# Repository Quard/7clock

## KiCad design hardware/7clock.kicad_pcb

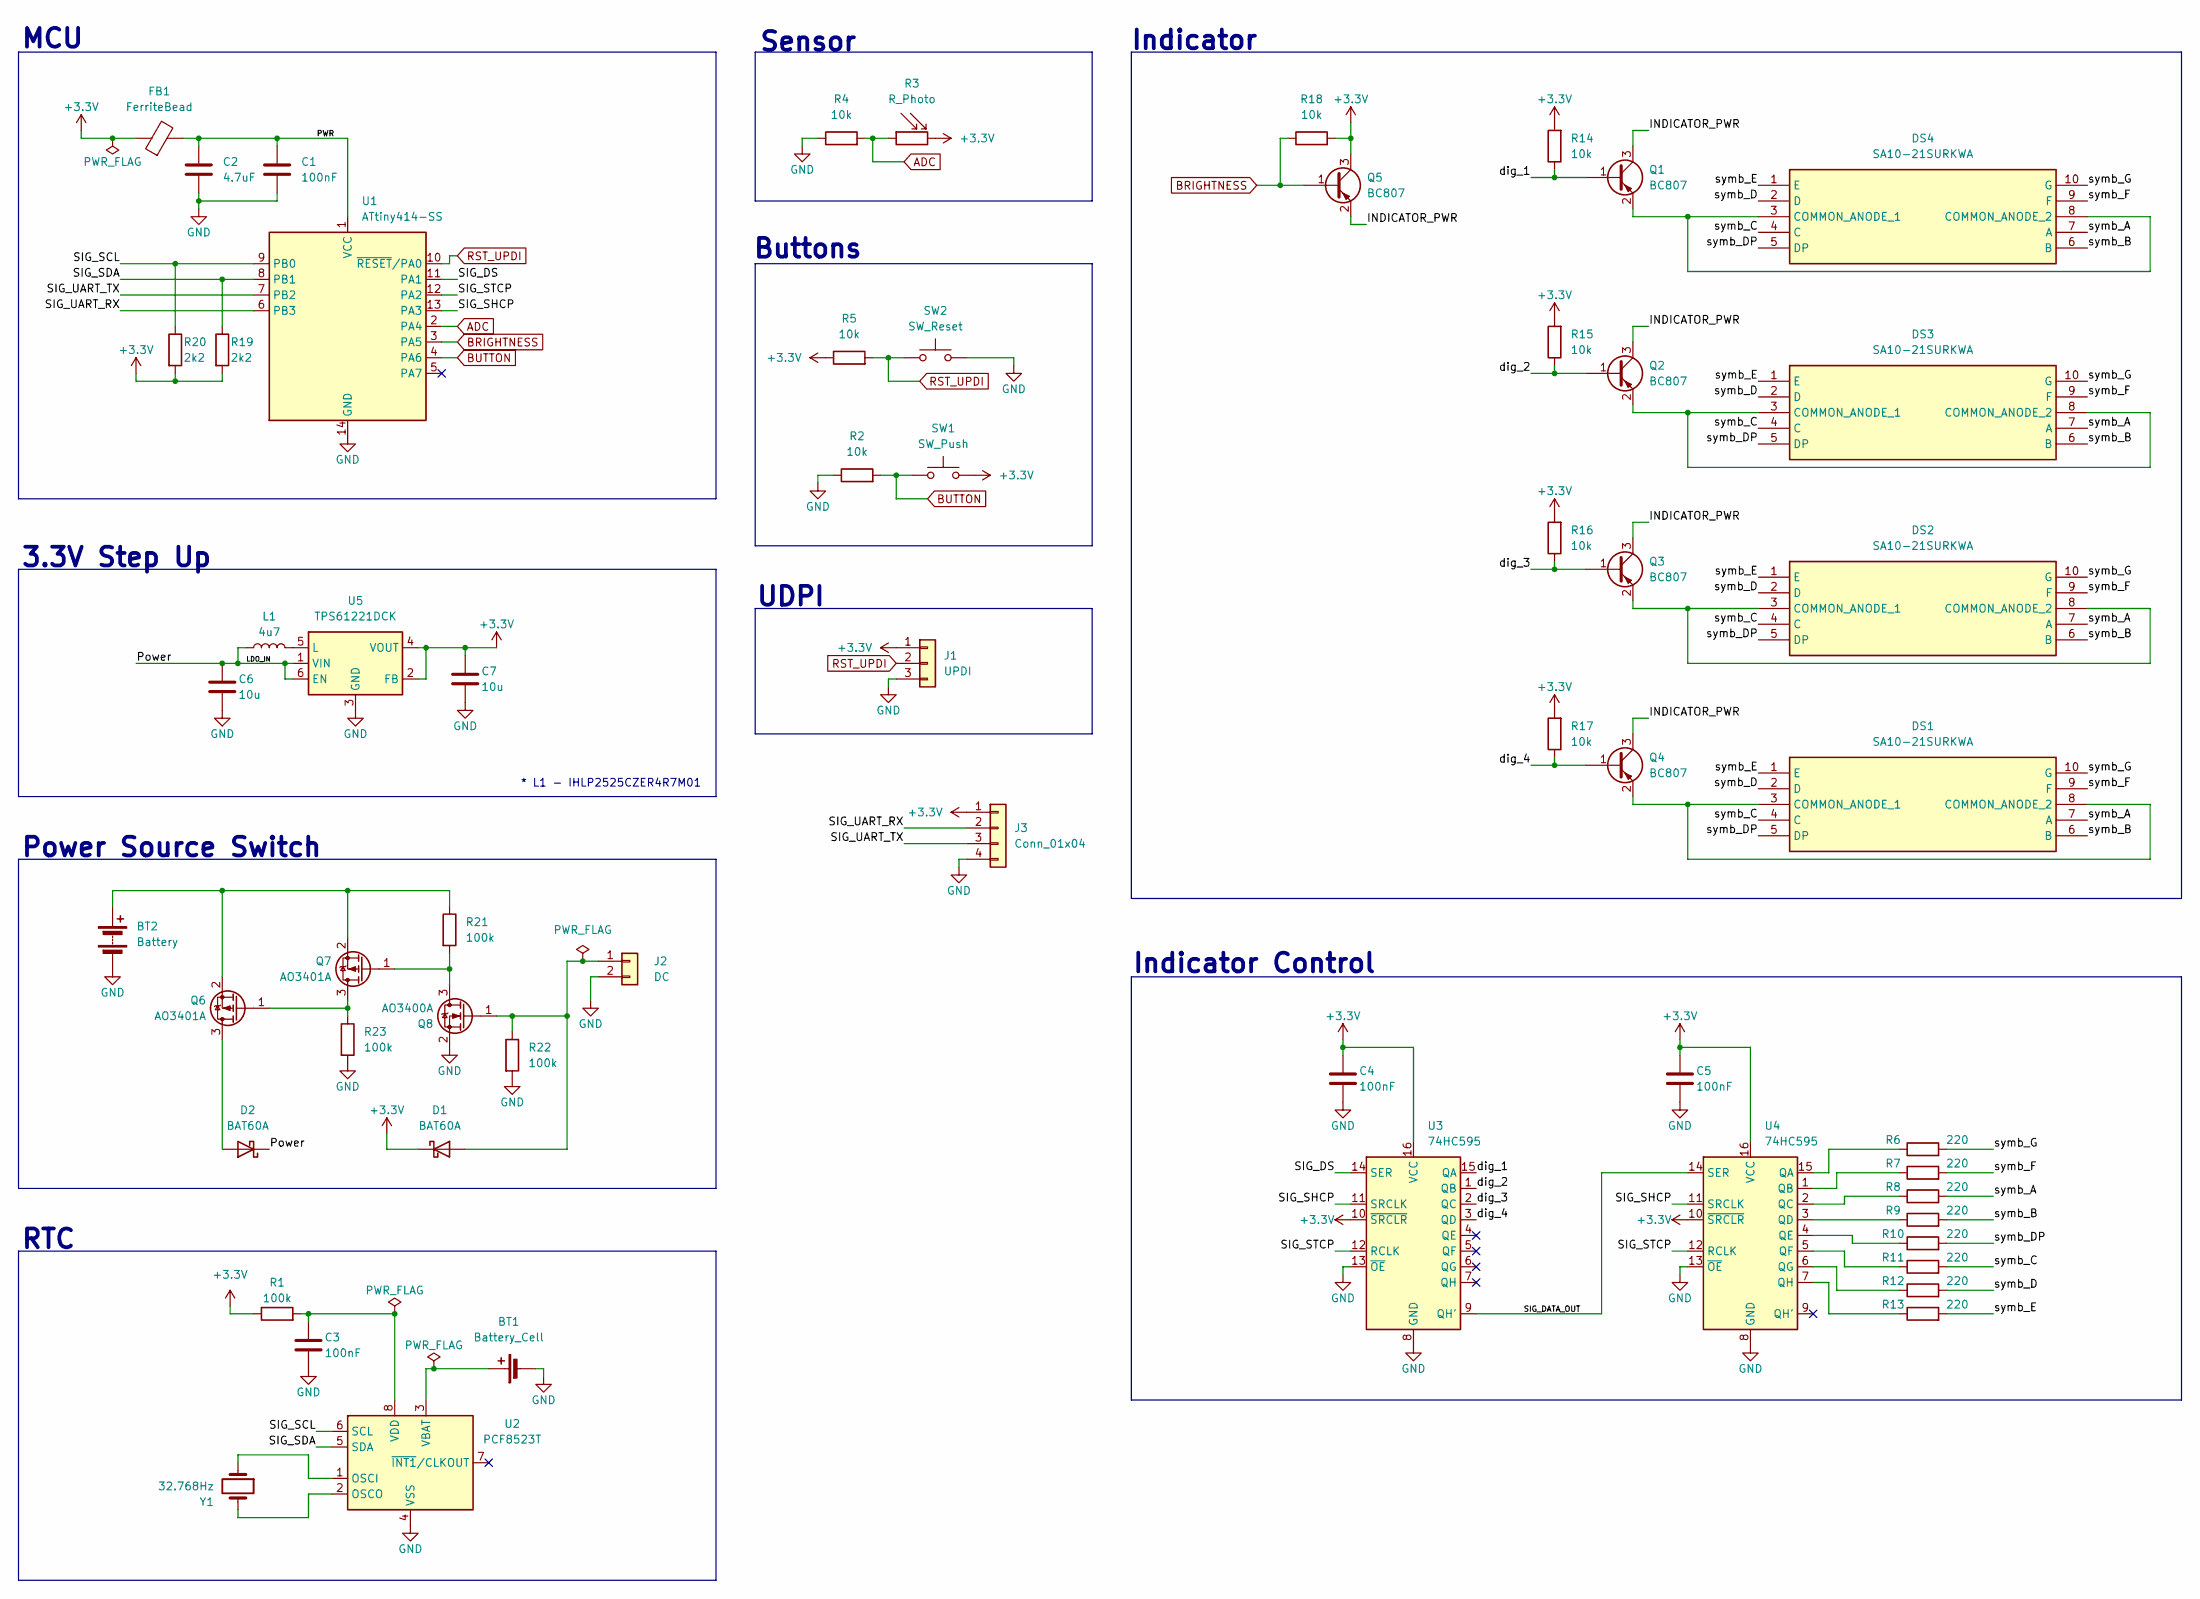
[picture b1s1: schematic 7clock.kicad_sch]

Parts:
BT1: Battery_Cell; CR1220D-011
BT2: Battery; PinHeader_1x02_P2.54mm_Vertical
C1, C3, C4, C5: 100nF; C_0603_1608Metric
C2: 4.7uF; C_0805_2012Metric
C6, C7: 10u; C_0805_2012Metric
D1, D2: BAT60A; D_SOD-323
DS1, DS2, DS3, DS4: SA10-21SURKWA; DIP3040W75P254L2400H1050Q10N; Manufacturer_Part_Number SA10-21SURKWA; Mouser Part Number 604-SA10-21SURKWA
FB1: FerriteBead; L_0603_1608Metric
J1: UPDI; PinHeader_1x03_P2.54mm_Vertical
J2: DC; PinHeader_1x02_P2.54mm_Vertical
J3: Conn_01x04; PinHeader_1x04_P2.54mm_Vertical
L1: 4u7; L_Vishay_IHLP-2525
Q1, Q2, Q3, Q4, Q5: BC807; SOT-23
Q6, Q7: AO3401A; SOT-23
Q8: AO3400A; SOT-23
R1, R21, R22, R23: 100k; R_0603_1608Metric
R2, R4, R5, R14, R15, R16, R17, R18: 10k; R_0603_1608Metric
R3: R_Photo; PinHeader_1x02_P2.54mm_Vertical
R6, R7, R8, R9, R10, R11, R12, R13: 220; R_0603_1608Metric
R19, R20: 2k2; R_0603_1608Metric
SW1: SW_Push; SW_SPST_SKQG_WithoutStem
SW2: SW_Reset; SW_SPST_CK_RS282G05A3
U1: ATtiny414-SS; SOIC-14_3.9x8.7mm_P1.27mm
U2: PCF8523T; SOIC-8_3.9x4.9mm_P1.27mm
U3, U4: 74HC595; SO-16_3.9x9.9mm_P1.27mm
U5: TPS61221DCK; Texas_R-PDSO-G6
Y1: 32.768Hz; Crystal_C38-LF_D3.0mm_L8.0mm_Horizontal

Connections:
+3.3V: C4.1, C5.1, C7.1, D1.1 (K), FB1.1, J1.1, J3.1, Q5.3 (C), R1.1, R3.2, R5.1, R14.2, R15.2, R16.2, R17.2, R18.2, R19.2, R20.2, SW1.2, U3.10 (~SRCLR), U3.16 (VCC), U4.10 (~SRCLR), U4.16 (VCC), U5.2 (FB), U5.4 (VOUT)
/INDICATOR_PWR: Q1.3 (C), Q2.3 (C), Q3.3 (C), Q4.3 (C), Q5.2 (E)
/LDO_IN: C6.1, D2.1 (K), L1.1, U5.1 (VIN), U5.6 (EN)
/PWR: C1.1, C2.1, FB1.2, U1.1 (VCC)
/SIG_DATA_OUT: U3.9 (QH'), U4.14 (SER)
/SIG_DS: U1.11 (PA1), U3.14 (SER)
/SIG_SCL: R20.1, U1.9 (PB0), U2.6 (SCL)
/SIG_SDA: R19.1, U1.8 (PB1), U2.5 (SDA)
/SIG_SHCP: U1.13 (PA3), U3.11 (SRCLK), U4.11 (SRCLK)
/SIG_STCP: U1.12 (PA2), U3.12 (RCLK), U4.12 (RCLK)
/SIG_UART_RX: J3.2, U1.6 (PB3)
/SIG_UART_TX: J3.3, U1.7 (PB2)
/dig_1: Q1.1 (B), R14.1, U3.15 (QA)
/dig_2: Q2.1 (B), R15.1, U3.1 (QB)
/dig_3: Q3.1 (B), R16.1, U3.2 (QC)
/dig_4: Q4.1 (B), R17.1, U3.3 (QD)
/symb_A: DS1.7 (A), DS2.7 (A), DS3.7 (A), DS4.7 (A), R8.2
/symb_B: DS1.6 (B), DS2.6 (B), DS3.6 (B), DS4.6 (B), R9.2
/symb_C: DS1.4 (C), DS2.4 (C), DS3.4 (C), DS4.4 (C), R11.2
/symb_D: DS1.2 (D), DS2.2 (D), DS3.2 (D), DS4.2 (D), R12.2
/symb_DP: DS1.5 (DP), DS2.5 (DP), DS3.5 (DP), DS4.5 (DP), R10.2
/symb_E: DS1.1 (E), DS2.1 (E), DS3.1 (E), DS4.1 (E), R13.2
/symb_F: DS1.9 (F), DS2.9 (F), DS3.9 (F), DS4.9 (F), R7.2
/symb_G: DS1.10 (G), DS2.10 (G), DS3.10 (G), DS4.10 (G), R6.2
ADC: R3.1, R4.2, U1.2 (PA4)
BRIGHTNESS: Q5.1 (B), R18.1, U1.3 (PA5)
BUTTON: R2.2, SW1.1, U1.4 (PA6)
GND: BT1.2 (-), BT2.2 (-), C1.2, C2.2, C3.2, C4.2, C5.2, C6.2, C7.2, J1.3, J2.2, J3.4, Q8.2 (S), R2.1, R4.1, R22.2, R23.2, SW2.2, U1.14 (GND), U2.4 (VSS), U3.8 (GND), U3.13 (~OE), U4.8 (GND), U4.13 (~OE), U5.3 (GND)
unnamed: BT1.1 (+), U2.3 (VBAT)
unnamed: BT2.1 (+), Q6.2 (S), Q7.2 (S), R21.1
unnamed: D1.2 (A), J2.1, Q8.1 (G), R22.1
unnamed: D2.2 (A), Q6.3 (D)
unnamed: DS1.3 (COMMON_ANODE_1), DS1.8 (COMMON_ANODE_2), Q4.2 (E)
unnamed: DS2.3 (COMMON_ANODE_1), DS2.8 (COMMON_ANODE_2), Q3.2 (E)
unnamed: DS3.3 (COMMON_ANODE_1), DS3.8 (COMMON_ANODE_2), Q2.2 (E)
unnamed: DS4.3 (COMMON_ANODE_1), DS4.8 (COMMON_ANODE_2), Q1.2 (E)
unnamed: Q6.1 (G), Q7.3 (D), R23.1
unnamed: Q7.1 (G), Q8.3 (D), R21.2
unnamed: U2.1 (OSCI), Y1.1
unnamed: U2.2 (OSCO), Y1.2
unnamed: C3.1, R1.2, U2.8 (VDD)
unnamed: R6.1, U4.15 (QA)
unnamed: R7.1, U4.1 (QB)
unnamed: R8.1, U4.2 (QC)
unnamed: R9.1, U4.3 (QD)
unnamed: R10.1, U4.4 (QE)
unnamed: R11.1, U4.5 (QF)
unnamed: R12.1, U4.6 (QG)
unnamed: R13.1, U4.7 (QH)
unnamed: L1.2, U5.5 (L)
RST_UPDI: J1.2, R5.2, SW2.1, U1.10 (~RESET/PA0)

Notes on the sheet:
Indicator Control
MCU
Indicator
Power Source Switch
* L1 - IHLP2525CZER4R7M01
3.3V Step Up
Sensor
RTC
UDPI
Buttons

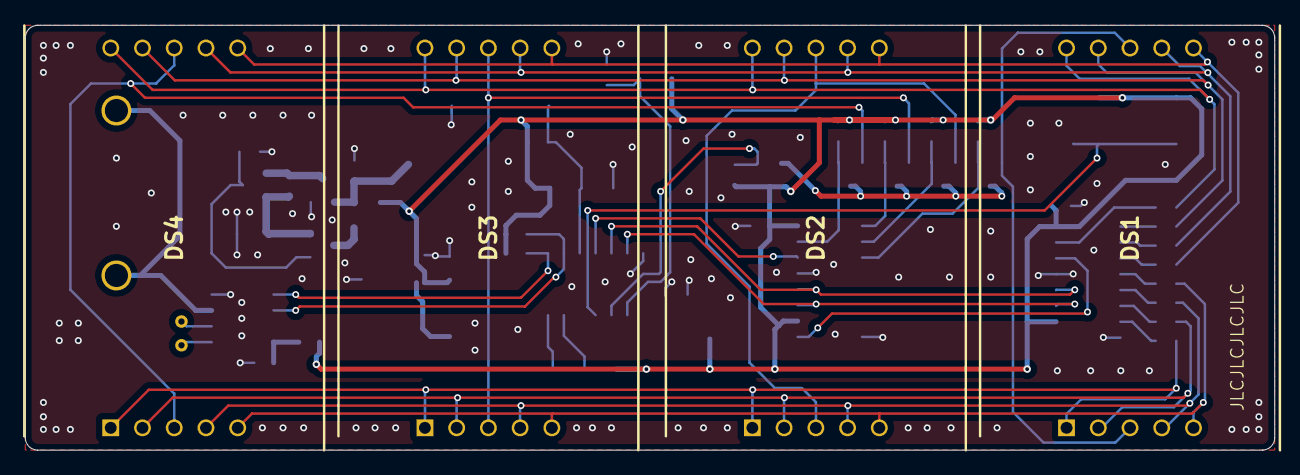
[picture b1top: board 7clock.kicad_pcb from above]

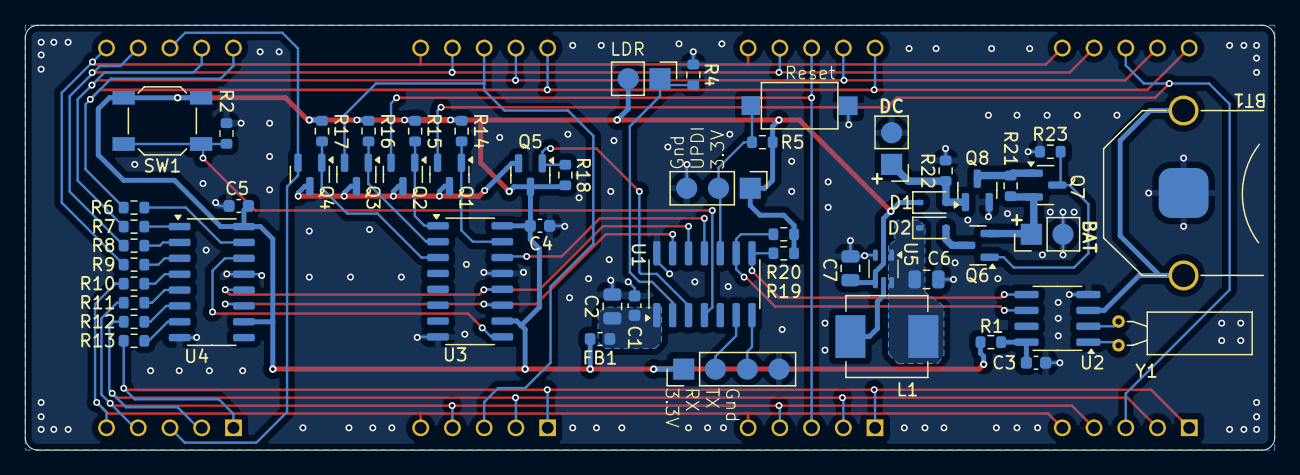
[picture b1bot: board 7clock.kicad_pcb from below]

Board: 2 copper layers, 100.0 x 34.0 mm, 59 parts (55 on the bottom side), 51 nets.

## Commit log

2023-02-01 pic configuration and simple display driver
2023-02-01 show clock using ds1302
2023-02-01 control brightness using ldr sensor
2023-02-03 use interrupt for timer1 and spi
2023-02-03 use button to control min brightness
2023-02-04 change file structure to keep not only firmware
2023-02-04 state machine to setup clock via one button
2023-02-04 clock dot blink
2023-02-04 fix timer1 freq
2024-06-29 fix button according to the schematic
2024-07-02 pic: use analog value from ldr to control brightness
2024-09-12 WIP avr version
2024-09-12 WIP schematic and pcb for avr version
2024-09-12 WIP avr reformat code
2024-09-13 WIP avr processing button and additional timer like systick
2024-09-13 WIP avr add state machine to configure the time
2024-09-13 avr fix showing clock after setup the time
2024-10-06 avr reconfigure rtc chip on startup if needed to use backup batter
